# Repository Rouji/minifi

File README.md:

# minifi

Fork of the [chocofi](https://github.com/pashutk/chocofi) for Choc Mini (PG1232) through-PCB switches.

Otherwise basically the same as the chocofi, except I'm pretty sure the case won't fit this anymore. (I haven't tested it though)

# Artifacts

Gerbers are in the [GitHub releases](https://github.com/Rouji/minifi/releases)

# Firmware

The chocofi is wired like a corne, and uses firmware built for the "corne" shield (at least for ZMK).  
Though re-routed, wiring is identical to the chocofi, so you building firmware for this is the same.  

**Note:** The corne has an extra pinky column, so you need to write your keymap as if those columns were there, and they just get ignored. 

# By the way

Recommended batteries:

- [Nice nano docs](https://nicekeyboards.com/docs/nice-nano/#recommended-batteries-and-sockets) explains some basics
- [nRFmicro wiki](https://github.com/joric/nrfmicro/wiki/Batteries#301230) contains links to Aliexpress

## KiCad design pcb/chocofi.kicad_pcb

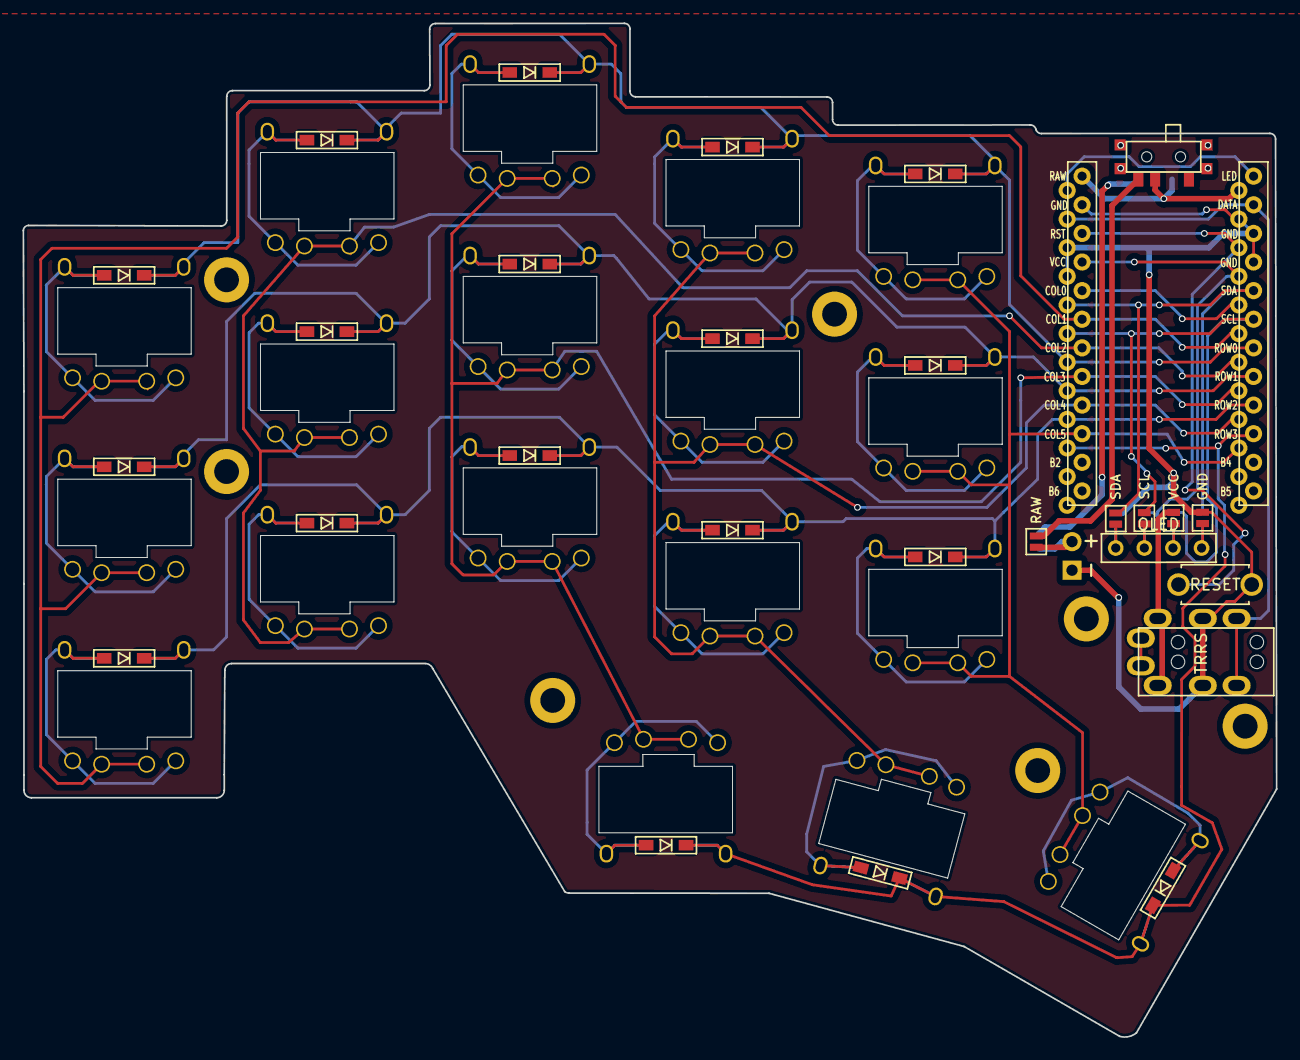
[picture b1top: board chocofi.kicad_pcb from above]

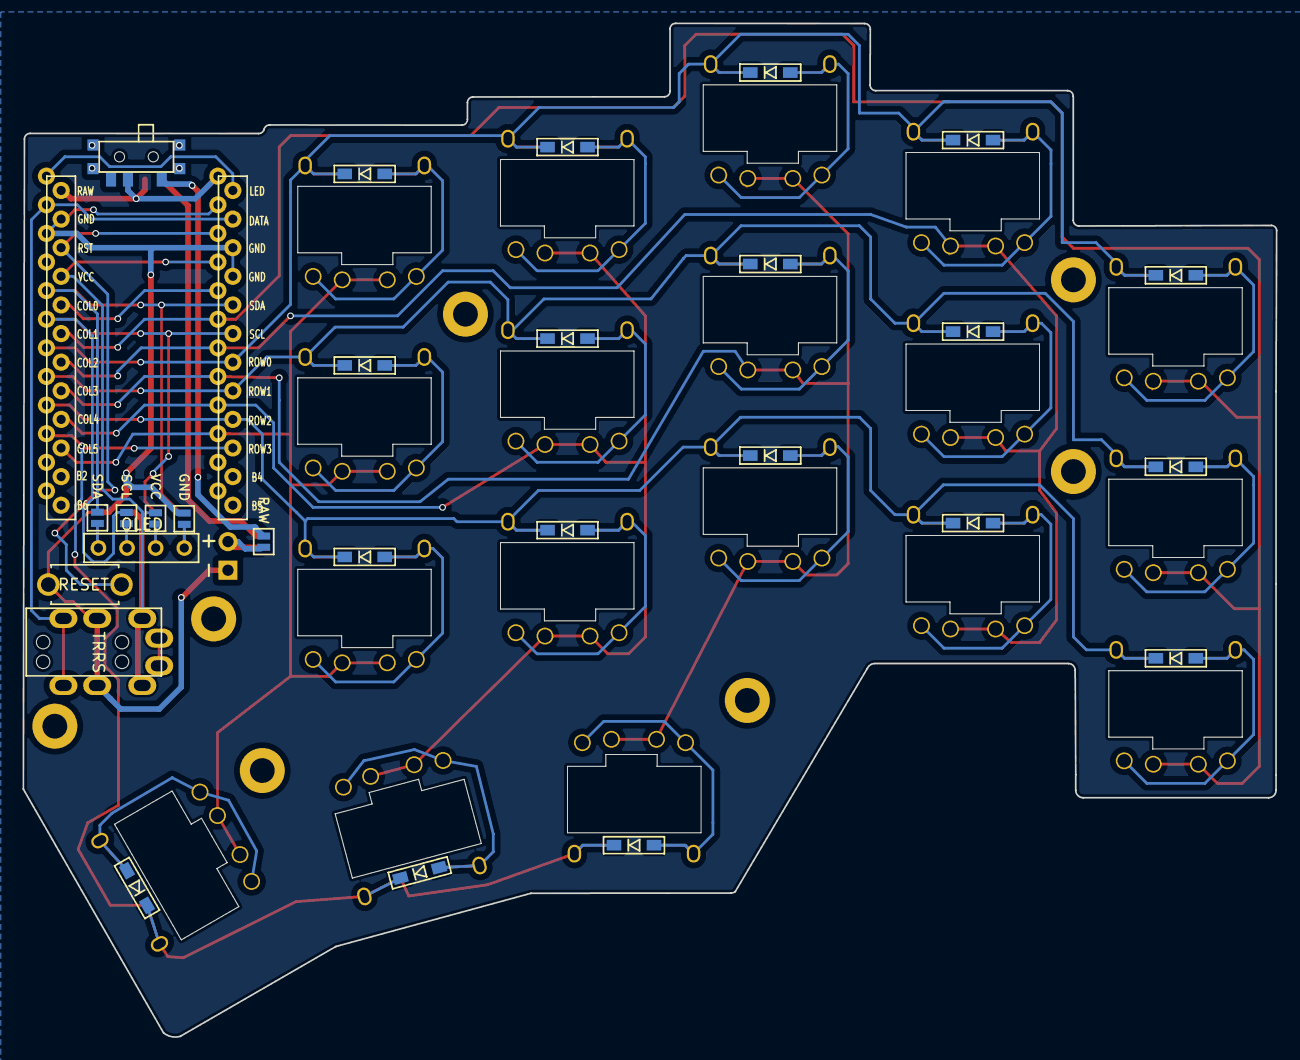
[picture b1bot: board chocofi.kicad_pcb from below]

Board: 2 copper layers, 111.3 x 90.0 mm, 60 parts (23 on the bottom side), 40 nets.

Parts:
D2, D3, D4, D5, D6, D8, D9, D10, D11, D12, D14, D15, D16, D17, D18, D19, D20, D21: D; D3_TH_SMD
H1: h1; LEGO_HOLE
J1: MJ-4PP-9
J2: OLED
J3: Conn_01x02_Female; Battery_TH
JP6, JP61: SDA; Jumper
JP61#2, JP62#2: RAW; Jumper
JP62, JP68: GND; Jumper
JP63, JP66: SCL; Jumper
JP64, JP65: VCC; Jumper
RSW1: Val**; ResetSW
SW1, SW2#2: SW_SPDT; SW_SPDT+H-MSK12C01_hor(7pin_SMD)
SW2, SW3, SW4, SW5, SW6, SW8, SW9, SW10, SW11, SW12, SW14, SW15, SW16, SW17, SW18, SW19, SW20, SW21: SW_PUSH; SW_Kailh_Choc_Mini_1.00u_reversible
U1: ProMicro; ProMicro_v2
h2: h2; LEGO_HOLE
h3: h3; LEGO_HOLE
h4: h4; LEGO_HOLE
h5: h5; LEGO_HOLE
h6: h6; LEGO_HOLE
h7: h7; LEGO_HOLE

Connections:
BAT_PLUS: J3.2, JP61#2.2, JP62#2.2
GND: J1.C, J3.1, JP62.1, JP68.1, RSW1.1, U1.3, U1.4, U1.23
unnamed: D2.2, SW2.2
unnamed: D3.2, SW3.2
unnamed: D4.2, SW4.2
unnamed: D5.2, SW5.2
unnamed: D6.2, SW6.2
unnamed: D8.2, SW8.2
unnamed: D9.2, SW9.2
unnamed: D10.2, SW10.2
unnamed: D11.2, SW11.2
unnamed: D12.2, SW12.2
unnamed: D14.2, SW14.2
unnamed: D15.2, SW15.2
unnamed: D16.2, SW16.2
unnamed: D17.2, SW17.2
unnamed: D18.2, SW18.2
unnamed: D19.2, SW19.2
unnamed: D20.2, SW20.2
unnamed: D21.2, SW21.2
unnamed: J2.3, JP65.2, JP66.2
unnamed: J2.4, JP6.2, JP68.2
unnamed: J2.2, JP63.2, JP64.2
unnamed: J2.1, JP61.2, JP62.2
unnamed: SW1.2 (B), SW2#2.2 (B), U1.24
SCL: JP63.1, JP66.1, U1.6
SDA: JP6.1, JP61.1, U1.5
SW_RAW_2: JP61#2.1, SW1.3 (C)
VCC: J1.D, JP64.1, JP65.1, U1.21
col1: SW2.1, SW8.1, SW14.1, U1.19
col2: SW3.1, SW9.1, SW15.1, U1.18
col3: SW4.1, SW10.1, SW16.1, SW19.1, U1.17
col4: SW5.1, SW11.1, SW17.1, SW20.1, U1.16
col5: SW6.1, SW12.1, SW18.1, SW21.1, U1.15
data: J1.B, U1.2
reset: RSW1.2, U1.22
row0: D2.1, D3.1, D4.1, D5.1, D6.1, U1.7
row1: D8.1, D9.1, D10.1, D11.1, D12.1, U1.8
row2: D14.1, D15.1, D16.1, D17.1, D18.1, U1.9
row3: D19.1, D20.1, D21.1, U1.10

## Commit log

2024-09-23 swap switch footprints for choc mini ones + reroute
2024-09-23 rm gerber stuff
    belongs in releases, not the repo
2025-04-04 remove diode through-holes, move diode pads to led-hole
    through hole diodes obv. don't fit on the side the switches are on,
    and are taller than the feet on the other side.
    we're looking for thinness here, so through-hole diodes are out
    moved the diode pads so the (smd) diodes sit in the void choc minis have
    for LEDs
    also using the adjacent foot through-holes of the switch as a via for
2025-04-26 swap out images, rm case, update readme
2025-04-26 readme: add hint about firmware
2025-04-26 readme: add picture from top
